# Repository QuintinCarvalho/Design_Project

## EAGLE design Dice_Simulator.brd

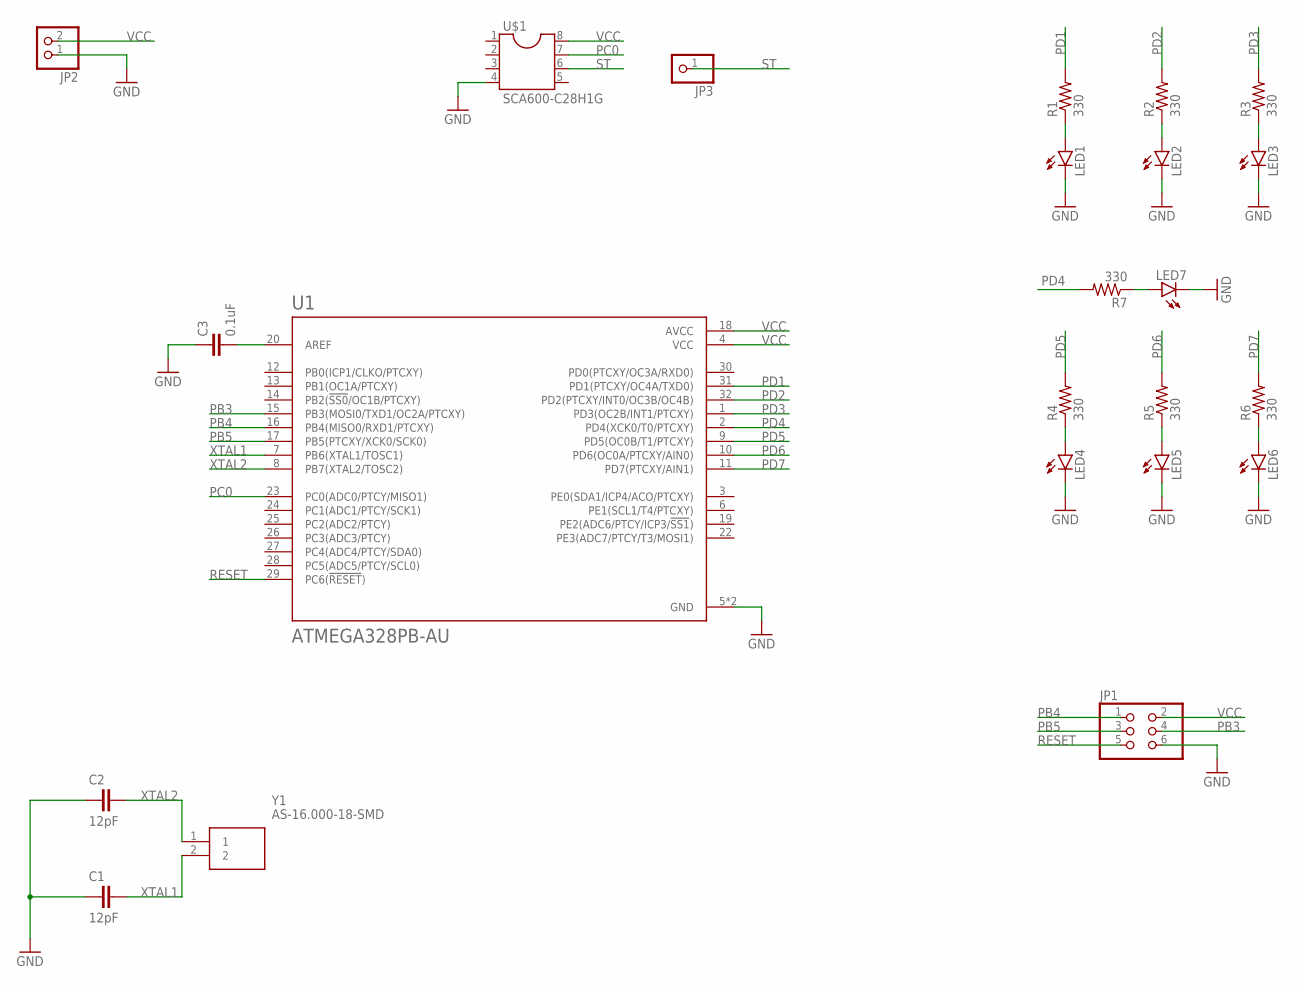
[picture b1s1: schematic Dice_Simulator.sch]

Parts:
C1, C2: 12pF; C0805
C3: 0.1uF; C0805
JP1: PINHD-2X3; 2X03
JP2: PINHD-1X2; 1X02
JP3: PINHD-1X1; 1X01
LED1, LED2, LED3, LED4, LED5, LED6, LED7: LEDCHIPLED_0805; CHIPLED_0805
R1, R2, R3, R4, R5, R6, R7: 330; M0805
U1: ATMEGA328PB-AU; QFP80P900X900X120-32N
U$1: SCA600-C28H1G
Y1: AS-16.000-18-SMD; HC-49

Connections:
GND: C1.1, C2.1, C3.1, JP1.6, JP2.1, LED1.C, LED2.C, LED3.C, LED4.C, LED5.C, LED6.C, LED7.C, U1.5 (GND), U1.21 (GND), U$1.4
unnamed: LED1.A, R1.1
unnamed: LED2.A, R2.1
unnamed: LED3.A, R3.1
unnamed: LED4.A, R4.1
unnamed: LED5.A, R5.1
unnamed: LED6.A, R6.1
unnamed: LED7.A, R7.1
unnamed: C3.2, U1.20 (AREF)
PB3: JP1.4, U1.15 (PB3(MOSI0/TXD1/OC2A/PTCXY))
PB4: JP1.1, U1.16 (PB4(MISO0/RXD1/PTCXY))
PB5: JP1.3, U1.17 (PB5(PTCXY/XCK0/SCK0))
PC0: U1.23 (PC0(ADC0/PTCY/MISO1)), U$1.7
PD1: R1.2, U1.31 (PD1(PTCXY/OC4A/TXD0))
PD2: R2.2, U1.32 (PD2(PTCXY/INT0/OC3B/OC4B))
PD3: R3.2, U1.1 (PD3(OC2B/INT1/PTCXY))
PD4: R7.2, U1.2 (PD4(XCK0/T0/PTCXY))
PD5: R4.2, U1.9 (PD5(OC0B/T1/PTCXY))
PD6: R5.2, U1.10 (PD6(OC0A/PTCXY/AIN0))
PD7: R6.2, U1.11 (PD7(PTCXY/AIN1))
RESET: JP1.5, U1.29 (PC6(!RESET!))
ST: JP3.1, U$1.6
VCC: JP1.2, JP2.2, U1.4 (VCC), U1.18 (AVCC), U$1.8
XTAL1: C1.2, U1.7 (PB6(XTAL1/TOSC1)), Y1.2
XTAL2: C2.2, U1.8 (PB7(XTAL2/TOSC2)), Y1.1

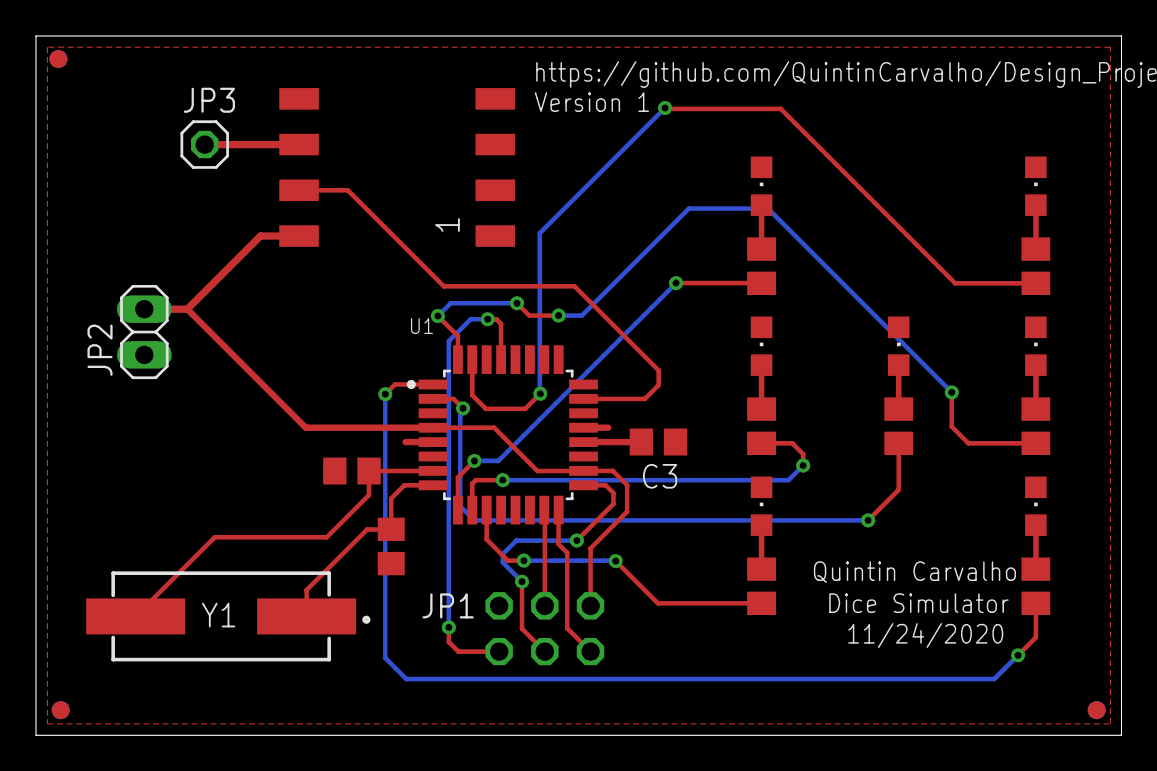
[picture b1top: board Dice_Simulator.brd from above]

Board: 2 copper layers, 60.3 x 38.8 mm, 26 parts (1 on the bottom side), 25 nets.

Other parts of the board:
U$2, U$3, U$4: FID-ROUND-1MM

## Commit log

2020-10-16 Create cam
2020-11-12 Create new
2020-11-12 Create CAMOutputs
2020-11-26 First commit Message
2020-11-27 added Firmware
2020-12-11 Create Demo Video Link
